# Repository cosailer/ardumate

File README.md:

# ardumate
this is a bigger arduboy clone with more features, the PCB has not been reviewed and may contain potential issues, please use at your discretion.

**specification:**\
mcu: atmega1284p\
usb-serial:ft232r\
width:78.74mm\
height:99.06mm

compared with original arduboy, the major differences are:

1, display:2.42 OLED\
2, mcu: atmega1284p(DIP), 128 KB flash, 4 KB EEPROM, 16 KB SRAM\
3, Sensors: ds18b20, H3LIS331\
4, a 24-serie I2C eeprom and a 25-serie flash\
5, inputs: 8 buttons instead of 4\
6, additional place for an encoder\
7, socket for a nRF24L01 module\
8, use ftdi ft232r usb serial to connect to PC\
9, SD card slot\
10, USB stack removed for arduboy library

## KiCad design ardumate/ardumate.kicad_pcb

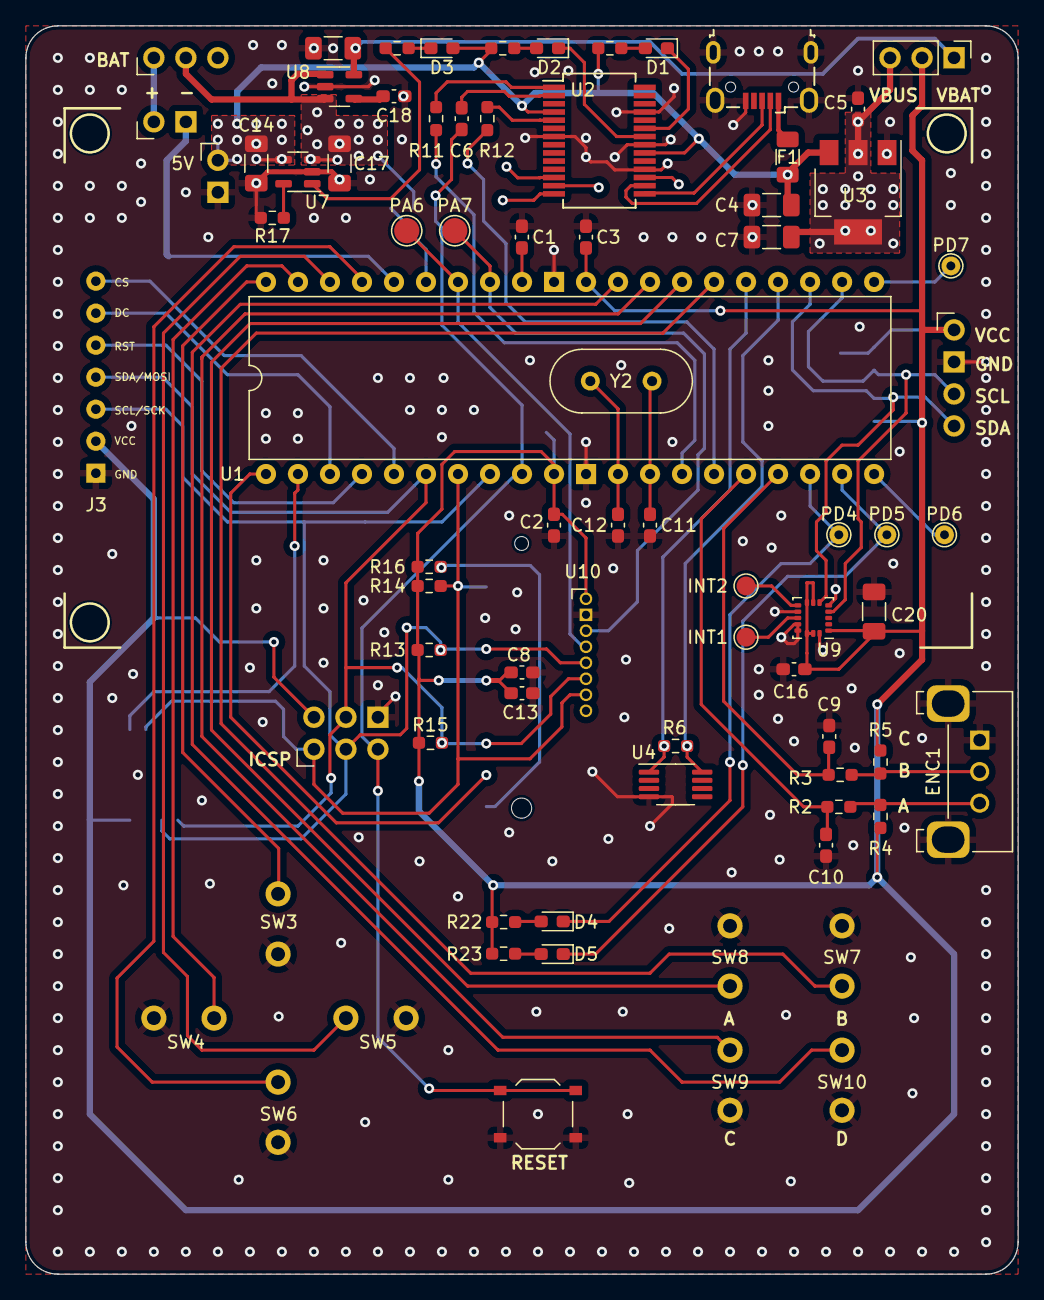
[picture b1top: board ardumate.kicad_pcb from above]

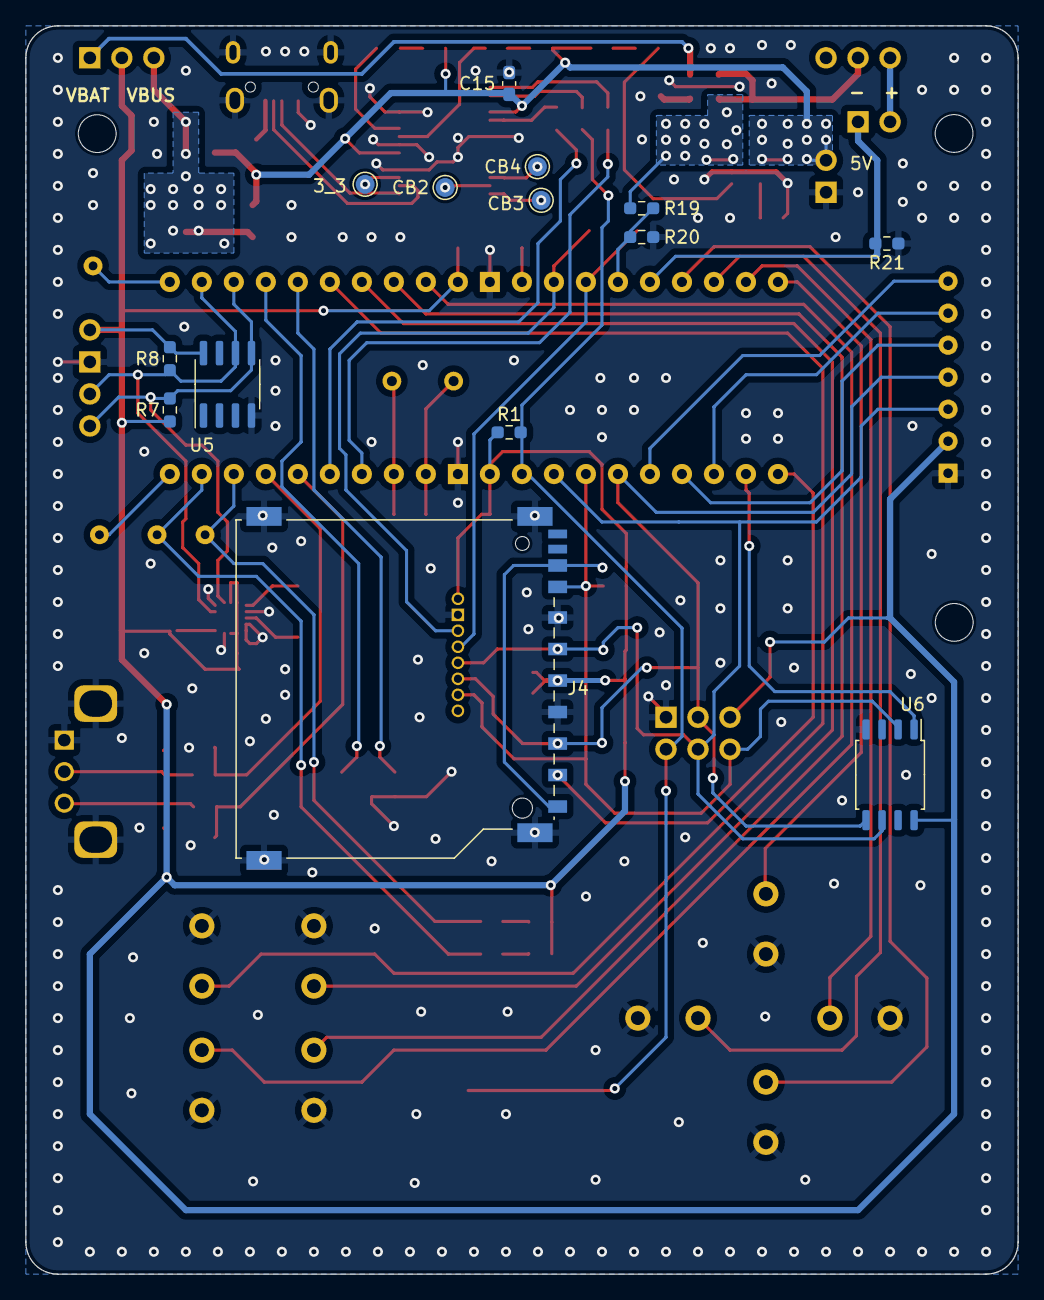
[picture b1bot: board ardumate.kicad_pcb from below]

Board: 2 copper layers, 78.7 x 99.1 mm, 91 parts (14 on the bottom side), 68 nets.

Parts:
3_3: TestPoint; TestPoint_Pad_D1.5mm
BT1: Battery_Cell; PinHeader_1x02_P2.54mm_Vertical
C1, C2, C3, C6, C8, C9, C10, C15, C16: 100nf; C_0603_1608Metric_Pad1.08x0.95mm_HandSolder
C4, C7, C14, C17: 4.7uf; C_1206_3216Metric_Pad1.33x1.80mm_HandSolder
C5: 1uf; C_0603_1608Metric_Pad1.08x0.95mm_HandSolder
C11, C12: 22pf; C_0603_1608Metric_Pad1.08x0.95mm_HandSolder
C13: 10uf; C_0603_1608Metric_Pad1.08x0.95mm_HandSolder
C18: 470pf; C_0603_1608Metric_Pad1.08x0.95mm_HandSolder
C19: 2.2uf; C_1206_3216Metric_Pad1.33x1.80mm_HandSolder
C20: 10uf; C_1206_3216Metric_Pad1.33x1.80mm_HandSolder
CB2, CB3, CB4: TestPoint; TestPoint_Pad_D1.5mm
D1, D2, D3, D4, D5: LED; LED_0603_1608Metric_Pad1.05x0.95mm_HandSolder
ENC1: RotaryEncoder; RotaryEncoder_Bourns_Horizontal_PEC12R-2xxxF-Nxxxx
EXT1: Battery_Cell; PinHeader_1x02_P2.54mm_Vertical
F1: Polyfuse; Fuse_1206_3216Metric
INT1, INT2: TestPoint; TestPoint_Pad_D1.5mm
J1: ICSP; PinHeader_2x03_P2.54mm_Vertical
J2: USB; USB_Micro-B_Wuerth_629105150521
J3: 2.4" OLED; DIYMORE.CC
J4: SD_Card; SD_TE_2041021
J5: PWR_SW; PinHeader_1x03_P2.54mm_Vertical
J6: BAT_SW; PinHeader_1x03_P2.54mm_Vertical
J7: I2C; PinHeader_1x04_P2.54mm_Vertical
PA6, PA7: TestPoint; TestPoint_Pad_D2.0mm
PD4, PD5, PD6, PD7: TestPoint; TestPoint_THTPad_D1.5mm_Drill0.7mm
R1, R19, R20: 100K; R_0603_1608Metric_Pad0.98x0.95mm_HandSolder
R2, R3, R4, R5, R7, R8, R13, R14, R15, R16: 10K; R_0603_1608Metric_Pad0.98x0.95mm_HandSolder
R6: 2K; R_0603_1608Metric_Pad0.98x0.95mm_HandSolder
R9, R10, R11, R12, R22, R23: 500R; R_0603_1608Metric_Pad0.98x0.95mm_HandSolder
R17: 5K; R_0603_1608Metric_Pad0.98x0.95mm_HandSolder
R18: 470; R_0603_1608Metric_Pad0.98x0.95mm_HandSolder
R21: 1; R_0603_1608Metric_Pad0.98x0.95mm_HandSolder
RST1: SW_Push; SW_Push_1P1T_XKB_TS-1187A
SW3, SW4, SW5, SW6, SW7, SW8, SW9, SW10: SW_Push; Kailh_mute
U1: ATmega1284P-P; DIP-40_W15.24mm
U2: FT232RL; SSOP-28_5.3x10.2mm_P0.65mm
U3: AMS1117-3.3; SOT-223-3_TabPin2
U4: DS18B20U; MSOP-8_3x3mm_P0.65mm
U5: M24C02-FMN; SOIC-8_3.9x4.9mm_P1.27mm
U6: AT25xxx; SOIC-8_5.23x5.23mm_P1.27mm
U7: MCP73831-2-OT; SOT-23-5
U8: MIC5205-3.3YM5; SOT-23-5
U9: LIS331HH; LGA-16_3x3mm_P0.5mm_LayoutBorder3x5y
U10: NRF24L01_SMD; PinHeader_1x08_P1.27mm_Vertical
Y2: 20Mhz; Crystal_HC18-U_Vertical

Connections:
3V3_MCU: C2.1, C3.1, C8.1, C13.1, C16.1, C20.1, J1.2, J3.2, J4.4 (VDD), J5.2, J7.1, R1.1, R4.1, R5.1, R7.1, R8.1, R13.1, R14.1, R15.1, R16.1, R22.2, R23.2, U1.10 (VCC), U1.30 (AVCC), U5.8 (VCC), U6.8 (VCC), U9.1 (Vdd_IO), U9.7 (SA0/SDO), U9.8 (~CS), U9.14 (Vdd), U9.15 (Vdd), U10.1 (VCC_3.3V)
3V3_VBAT: C19.1, J5.1, U8.5 (OUT)
3V3_VBUS: C5.1, C7.1, J5.3, U3.2 (VO)
+5V: C4.1, C14.1, C15.1, D3.2 (A), EXT1.1, F1.2, R9.2, R10.2, U2.4 (VCCIO), U2.20 (VCC), U3.3 (VI), U7.4 (V_{DD})
AREF: C1.1, U1.32 (AREF)
BAT_ADC1: R19.2, R20.1, U1.35 (PA5)
BAT_ADC2: BT1.2 (-), R21.1, U1.36 (PA4)
DC: J3.6, U1.3 (PB2)
DS18B20: R6.2, U1.25 (PC3), U4.1 (DQ)
DS18B20_EN: R6.1, U1.24 (PC2), U4.8 (V_{DD})
ENA: C10.1, R2.1, U1.16 (PD2)
ENB: C9.1, R3.1, U1.17 (PD3)
FLASH_CS: U1.2 (PB1), U6.1 (~CS)
GND: C1.2, C2.2, C3.2, C4.2, C5.2, C7.2, C8.2, C9.2, C10.2, C11.2, C12.2, C13.2, C14.2, C15.2, C16.2, C17.2, C18.2, C19.2, C20.2, ENC1.C, ENC1.SH, EXT1.2, J1.6, J2.5 (GND), J2.6 (Shield), J3.1, J4.3 (VSS), J4.6 (VSS), J4.12 (SHELL1), J7.2, R17.2, R20.2, R21.2, RST1.1, SW3.2, SW4.2, SW5.2, SW6.2, SW7.2, SW8.2, SW9.2, SW10.2, U1.11 (GND), U1.31 (GND), U2.7 (GND), U2.18 (GND), U2.21 (GND), U2.25 (AGND), U3.1 (GND), U4.4 (GND), U5.4 (VSS), U6.4 (GND), U7.2 (V_{SS}), U8.2 (GND), U9.5 (GND), U9.10 (GND), U9.12 (GND), U9.13 (GND), U9.16 (GND), U10.2 (GND)
MISO: J1.1, J4.7 (DAT0), R14.2, U1.7 (PB6), U6.2 (MISO), U10.7 (MISO)
MOSI: J1.4, J3.4, J4.2 (CMD), R15.2, U1.6 (PB5), U6.5 (MOSI), U10.6 (MOSI)
unnamed: BT1.1 (+), J6.1
unnamed: D1.2 (A), R9.1
unnamed: D1.1 (K), U2.23 (CBUS0)
unnamed: D2.2 (A), R10.1
unnamed: D2.1 (K), U2.22 (CBUS1)
unnamed: D3.1 (K), R18.2
unnamed: D4.2 (A), R22.1
unnamed: D4.1 (K), PD4.1, U1.18 (PD4)
unnamed: D5.2 (A), R23.1
unnamed: D5.1 (K), PD5.1, U1.19 (PD5)
unnamed: ENC1.A, R2.2, R4.2
unnamed: ENC1.B, R3.2, R5.2
unnamed: J2.3 (D+), U2.15 (USBD+)
unnamed: J2.2 (D-), U2.16 (USBD-)
unnamed: F1.1, J2.1 (VBUS)
unnamed: J4.8 (DAT1), J4.9 (DAT2), R16.2
unnamed: C17.1, J6.2, R19.1, U7.3 (V_{BAT}), U8.1 (IN), U8.3 (EN)
unnamed: SW3.1, U1.40 (PA0)
unnamed: SW4.1, U1.39 (PA1)
unnamed: SW5.1, U1.38 (PA2)
unnamed: SW6.1, U1.37 (PA3)
unnamed: SW7.1, U1.26 (PC4)
unnamed: SW8.1, U1.27 (PC5)
unnamed: SW9.1, U1.28 (PC6)
unnamed: SW10.1, U1.29 (PC7)
unnamed: PD6.1, U1.20 (PD6)
unnamed: PD7.1, U1.21 (PD7)
unnamed: C11.1, U1.13 (XTAL1), Y2.1
unnamed: C12.1, U1.12 (XTAL2), Y2.2
unnamed: 3_3.1, U2.17 (3V3OUT)
unnamed: CB2.1, U2.13 (CBUS2)
unnamed: CB3.1, U2.14 (CBUS3)
unnamed: CB4.1, U2.12 (CBUS4)
unnamed: C6.1, U2.2 (DTR)
unnamed: R12.1, U2.5 (RXD)
unnamed: R11.1, U2.1 (TXD)
unnamed: R17.1, U7.5 (PROG)
unnamed: R18.1, U7.1 (STAT)
unnamed: C18.1, U8.4 (BP)
unnamed: INT1.1, U9.11 (INT1)
unnamed: INT2.1, U9.9 (INT2)
OLED_CS: J3.7, U1.5 (PB4)
OLED_RST: J3.5, U1.4 (PB3)
PA6: PA6.1, U1.34 (PA6), U10.4 (CSN)
PA7: PA7.1, U1.33 (PA7), U10.3 (CE)
RESET: C6.2, J1.5, R1.2, RST1.2, U1.9 (~RESET)
RX: R12.2, U1.15 (PD1)
SCK: J1.3, J3.3, J4.5 (CLK), R13.2, U1.8 (PB7), U6.6 (SCK), U10.5 (SCK)
SCL: J7.3, R8.2, U1.22 (PC0), U5.6 (SCL), U9.4 (SCL/SPC)
SDA: J7.4, R7.2, U1.23 (PC1), U5.5 (SDA), U9.6 (SDA/SDI)
SD_CS: J4.1 (CD/DAT3), U1.1 (PB0)
TX: R11.2, U1.14 (PD0)

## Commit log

2023-10-21 add pcb files
